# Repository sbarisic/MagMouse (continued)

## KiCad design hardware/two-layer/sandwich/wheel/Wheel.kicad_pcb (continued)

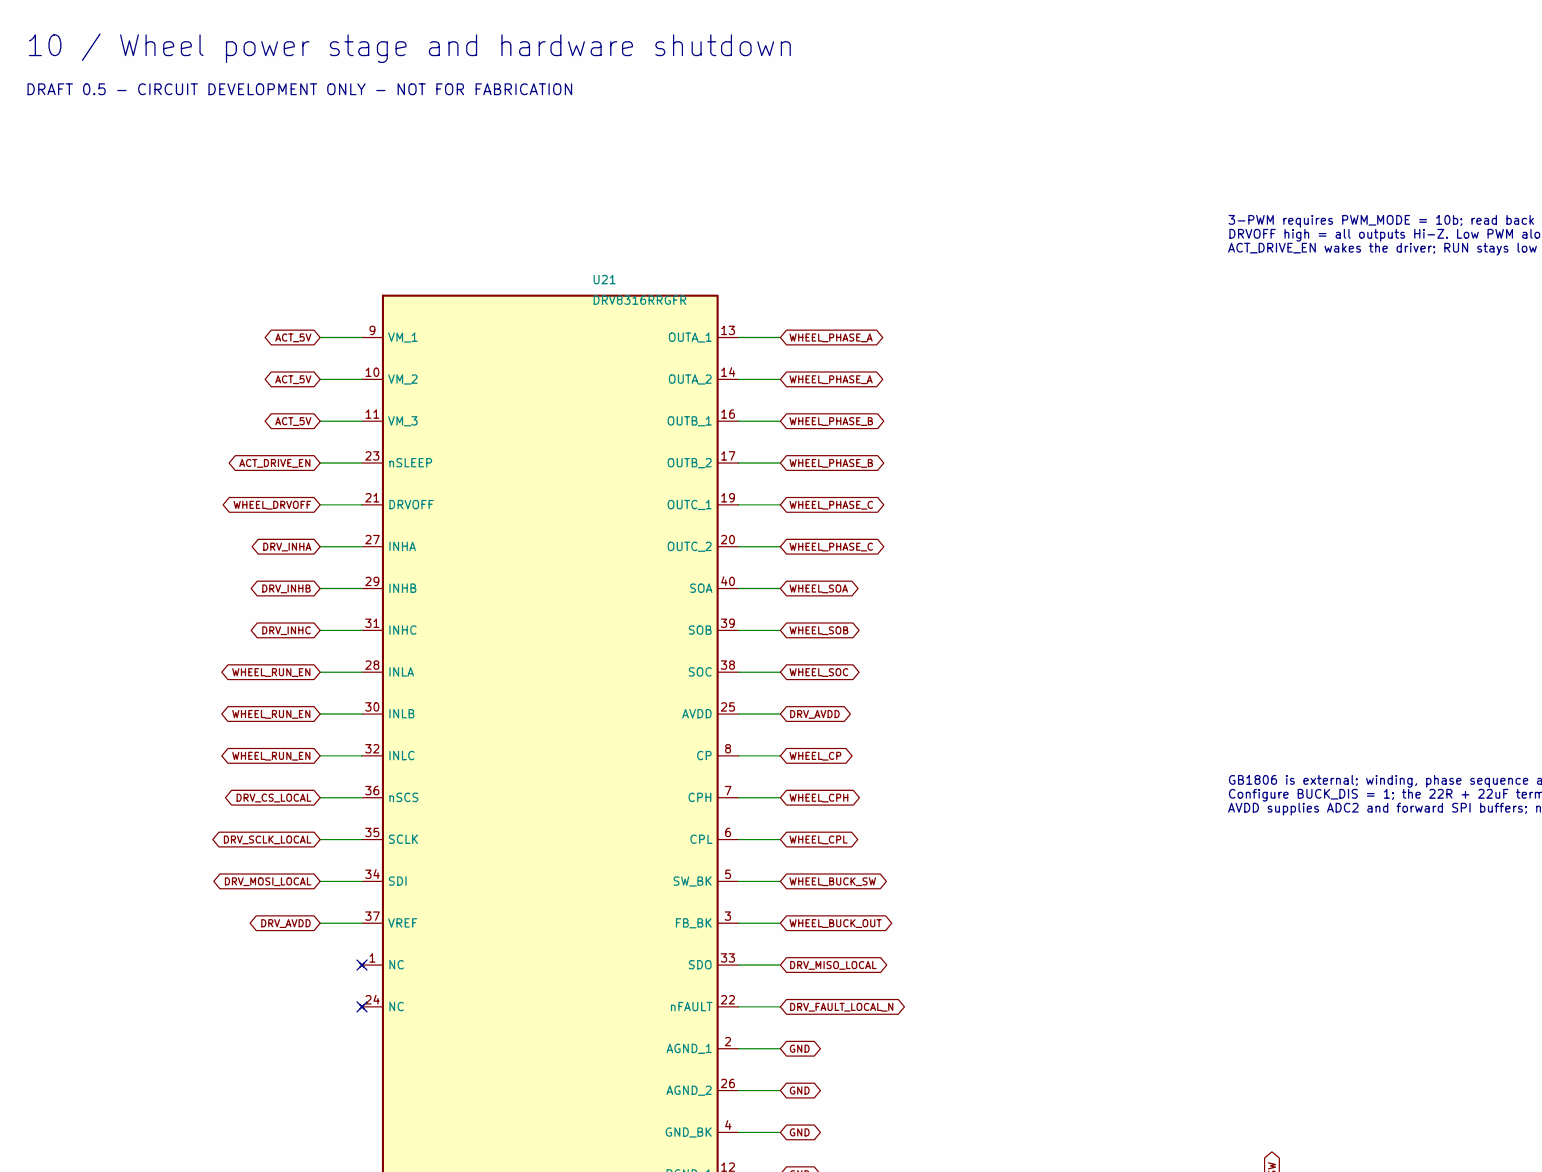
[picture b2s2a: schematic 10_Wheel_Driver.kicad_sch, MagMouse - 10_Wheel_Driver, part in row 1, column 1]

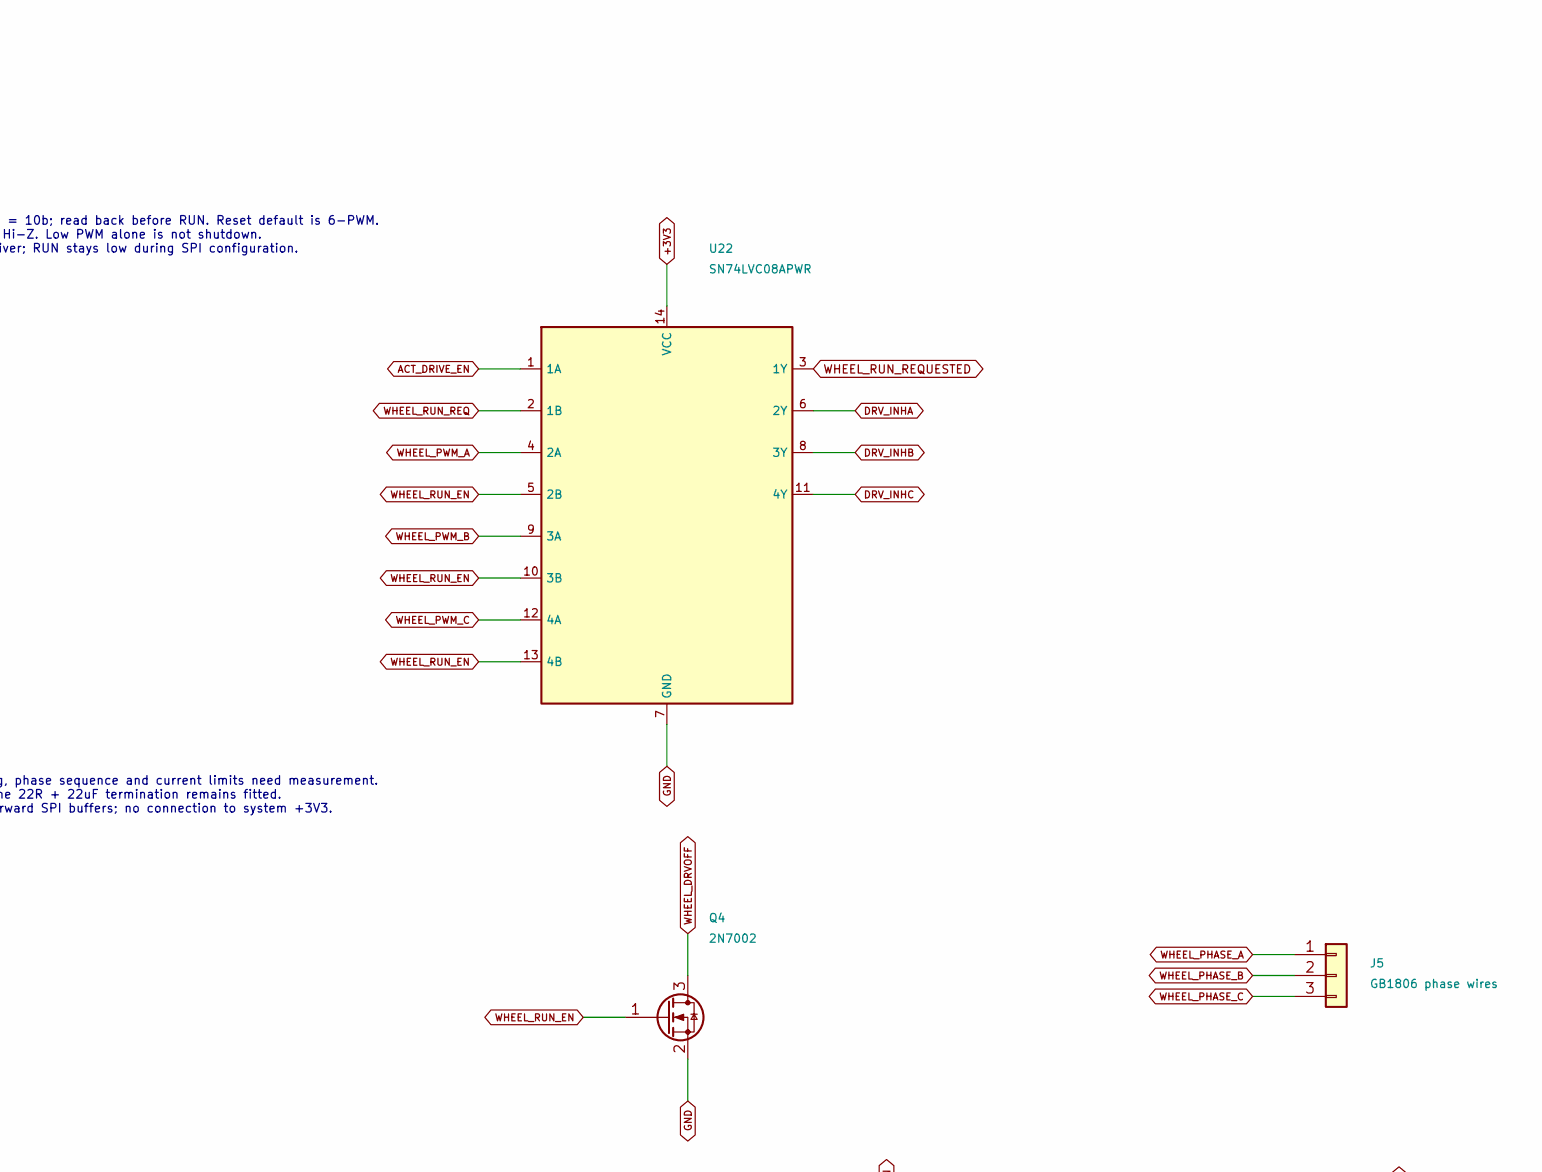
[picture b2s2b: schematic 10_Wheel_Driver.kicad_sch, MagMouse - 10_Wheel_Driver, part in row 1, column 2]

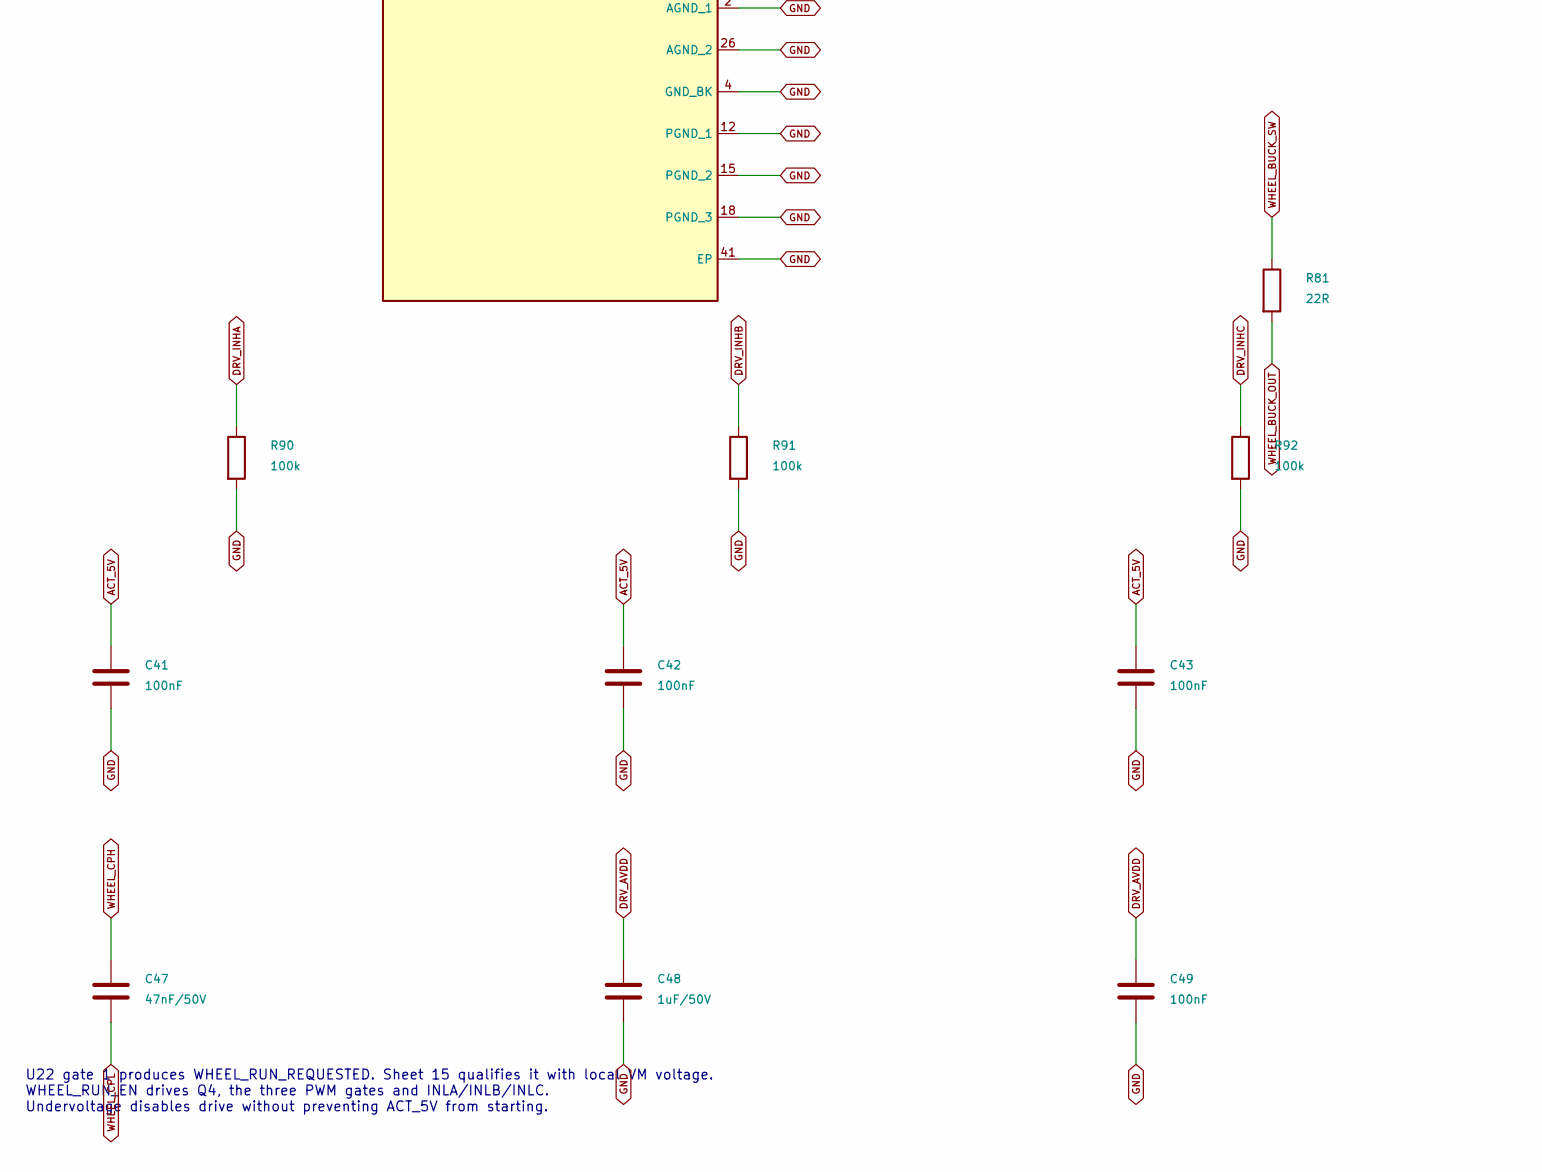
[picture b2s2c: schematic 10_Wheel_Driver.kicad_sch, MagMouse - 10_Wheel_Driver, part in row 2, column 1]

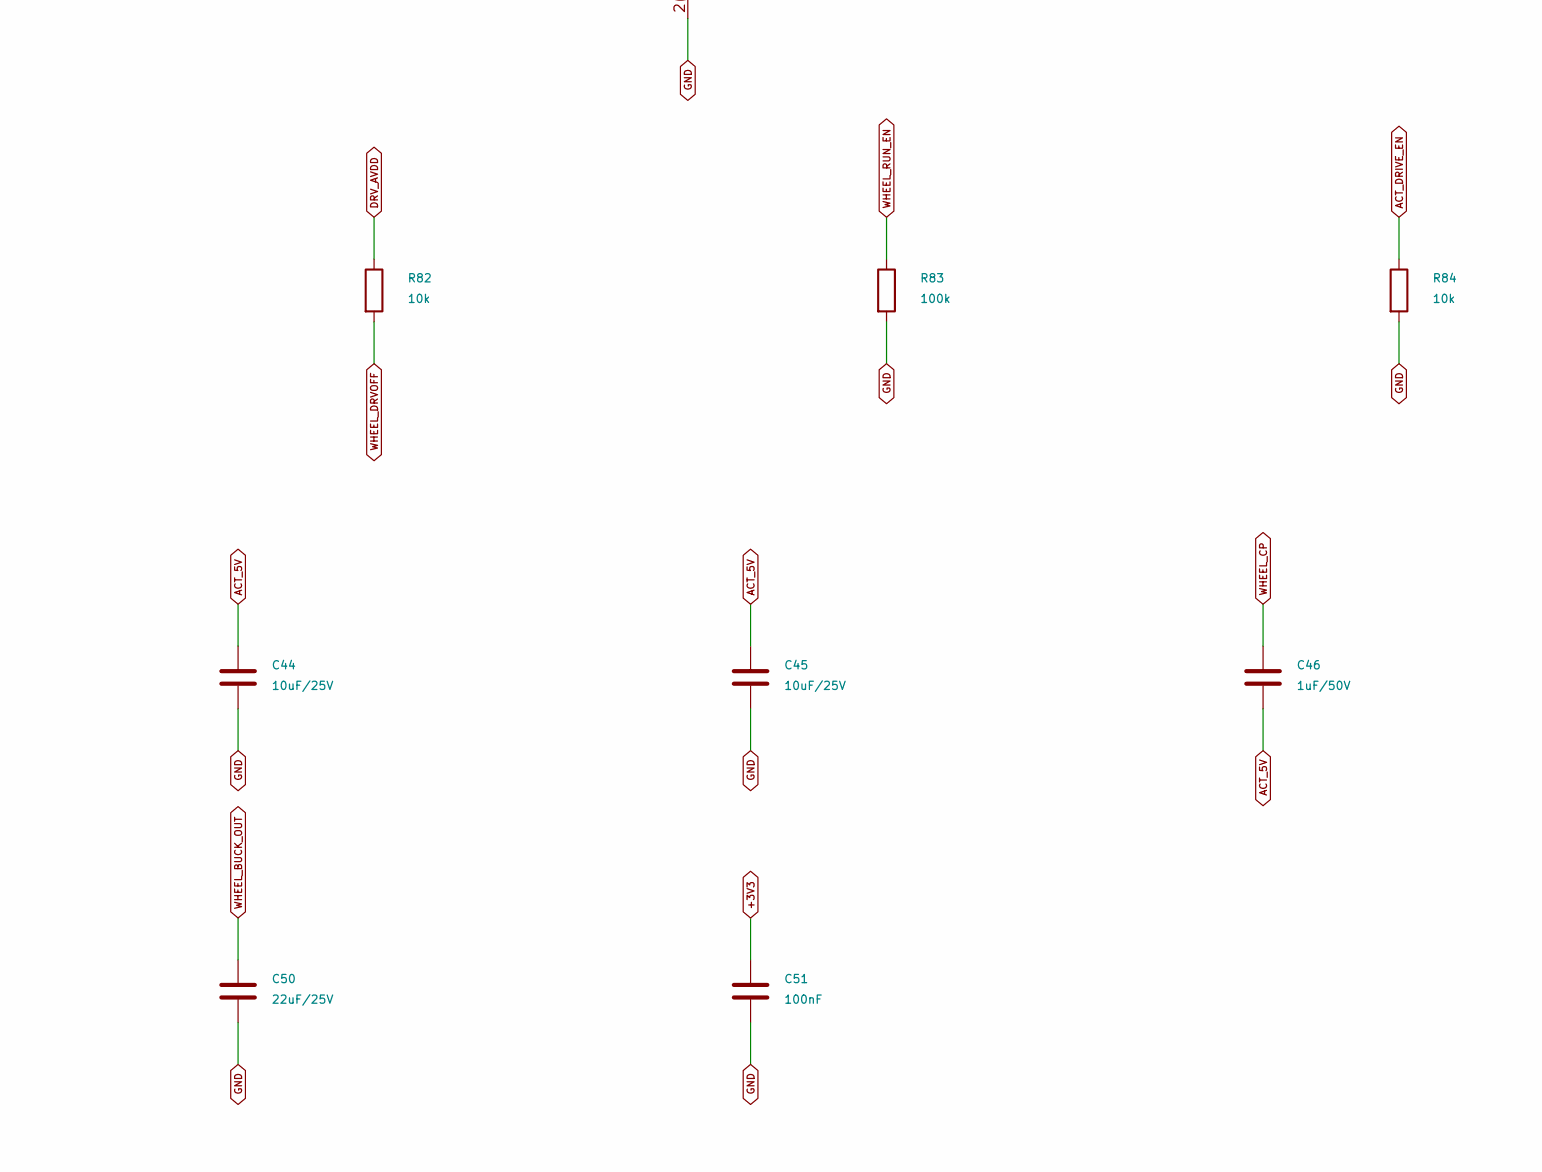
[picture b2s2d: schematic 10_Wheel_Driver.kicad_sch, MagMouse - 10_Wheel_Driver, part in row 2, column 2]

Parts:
C41, C42, C43, C49, C51: 100nF; C_1206_3216Metric; Rating 50 V, X7R, 10%; MPN CC1206KRX7R9BB104
C44, C45: 10uF/25V; C_1206_3216Metric; Rating 25 V, X5R, 10%; MPN CL31A106KAHNNNE
C46, C48: 1uF/50V; C_1206_3216Metric; Rating 50 V, X7R, 10%; MPN CL31B105KBHNNNE
C47: 47nF/50V; C_1206_3216Metric; Rating 50 V, X7R, 10%; MPN CC1206KRX7R9BB473
C50: 22uF/25V; C_1206_3216Metric; Rating 25 V, X5R, 10%; MPN CL31A226KAHNNNE
J5: GB1806 phase wires; MotorWire_3x1mm_P2.54mm
Q4: 2N7002; SOT-23; MPN 2N7002; LCSC C8545
R81: 22R; R_1206_3216Metric; Rating 0.25 W, 1%; MPN RC1206FR-0722RL
R82, R84: 10k; R_1206_3216Metric; Rating 0.25 W, 1%; MPN RC1206FR-0710KL
R83, R90, R91, R92: 100k; R_1206_3216Metric; Rating 0.25 W, 1%; MPN RC1206FR-07100KL
U21: DRV8316RRGFR; Texas_RGF0040E; MPN DRV8316RRGFR; LCSC C5218861
U22: SN74LVC08APWR; TSSOP-14_4.4x5mm_P0.65mm; MPN SN74LVC08APWR; LCSC C465737

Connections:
+3V3: C51.1, U22.14 (VCC); also elsewhere on the board
ACT_5V: C41.1, C42.1, C43.1, C44.1, C45.1, C46.2, U21.9 (VM_1), U21.10 (VM_2), U21.11 (VM_3); also elsewhere on the board
ACT_DRIVE_EN: R84.1, U21.23 (nSLEEP), U22.1 (1A); also elsewhere on the board
DRV_AVDD: C48.1, C49.1, R82.1, U21.25 (AVDD), U21.37 (VREF); also elsewhere on the board
DRV_CS_LOCAL: U21.36 (nSCS); also elsewhere on the board
DRV_FAULT_LOCAL_N: U21.22 (nFAULT); also elsewhere on the board
DRV_INHA: R90.1, U21.27 (INHA), U22.6 (2Y)
DRV_INHB: R91.1, U21.29 (INHB), U22.8 (3Y)
DRV_INHC: R92.1, U21.31 (INHC), U22.11 (4Y)
DRV_MISO_LOCAL: U21.33 (SDO); also elsewhere on the board
DRV_MOSI_LOCAL: U21.34 (SDI); also elsewhere on the board
DRV_SCLK_LOCAL: U21.35 (SCLK); also elsewhere on the board
GND: C41.2, C42.2, C43.2, C44.2, C45.2, C48.2, C49.2, C50.2, C51.2, Q4.2 (S), R83.2, R84.2, R90.2, R91.2, R92.2, U21.2 (AGND_1), U21.4 (GND_BK), U21.12 (PGND_1), U21.15 (PGND_2), U21.18 (PGND_3), U21.26 (AGND_2), U21.41 (EP), U22.7 (GND); also elsewhere on the board
WHEEL_BUCK_OUT: C50.1, R81.2, U21.3 (FB_BK)
WHEEL_BUCK_SW: R81.1, U21.5 (SW_BK)
WHEEL_CP: C46.1, U21.8 (CP)
WHEEL_CPH: C47.1, U21.7 (CPH)
WHEEL_CPL: C47.2, U21.6 (CPL)
WHEEL_DRVOFF: Q4.3 (D), R82.2, U21.21 (DRVOFF)
WHEEL_PHASE_A: J5.1, U21.13 (OUTA_1), U21.14 (OUTA_2)
WHEEL_PHASE_B: J5.2, U21.16 (OUTB_1), U21.17 (OUTB_2)
WHEEL_PHASE_C: J5.3, U21.19 (OUTC_1), U21.20 (OUTC_2)
WHEEL_PWM_A: U22.4 (2A); also elsewhere on the board
WHEEL_PWM_B: U22.9 (3A); also elsewhere on the board
WHEEL_PWM_C: U22.12 (4A); also elsewhere on the board
WHEEL_RUN_EN: Q4.1 (G), R83.1, U21.28 (INLA), U21.30 (INLB), U21.32 (INLC), U22.5 (2B), U22.10 (3B), U22.13 (4B); also elsewhere on the board
WHEEL_RUN_REQ: U22.2 (1B); also elsewhere on the board
WHEEL_RUN_REQUESTED: U22.3 (1Y); also elsewhere on the board
WHEEL_SOA: U21.40 (SOA); also elsewhere on the board
WHEEL_SOB: U21.39 (SOB); also elsewhere on the board
WHEEL_SOC: U21.38 (SOC); also elsewhere on the board

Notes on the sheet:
10 / Wheel power stage and hardware shutdown
DRAFT 0.5 - CIRCUIT DEVELOPMENT ONLY - NOT FOR FABRICATION
3-PWM requires PWM_MODE = 10b; read back before RUN. Reset default is 6-PWM. DRVOFF high = all outputs Hi-Z. Low PWM alone is not shutdown. ACT_DRIVE_EN wakes the driver; RUN stays low during SPI configuration.
GB1806 is external; winding, phase sequence and current limits need measurement. Configure BUCK_DIS = 1; the 22R + 22uF termination remains fitted. AVDD supplies ADC2 and forward SPI buffers; no connection to system +3V3.
U22 gate 1 produces WHEEL_RUN_REQUESTED. Sheet 15 qualifies it with local VM voltage. WHEEL_RUN_EN drives Q4, the three PWM gates and INLA/INLB/INLC. Undervoltage disables drive without preventing ACT_5V from starting.

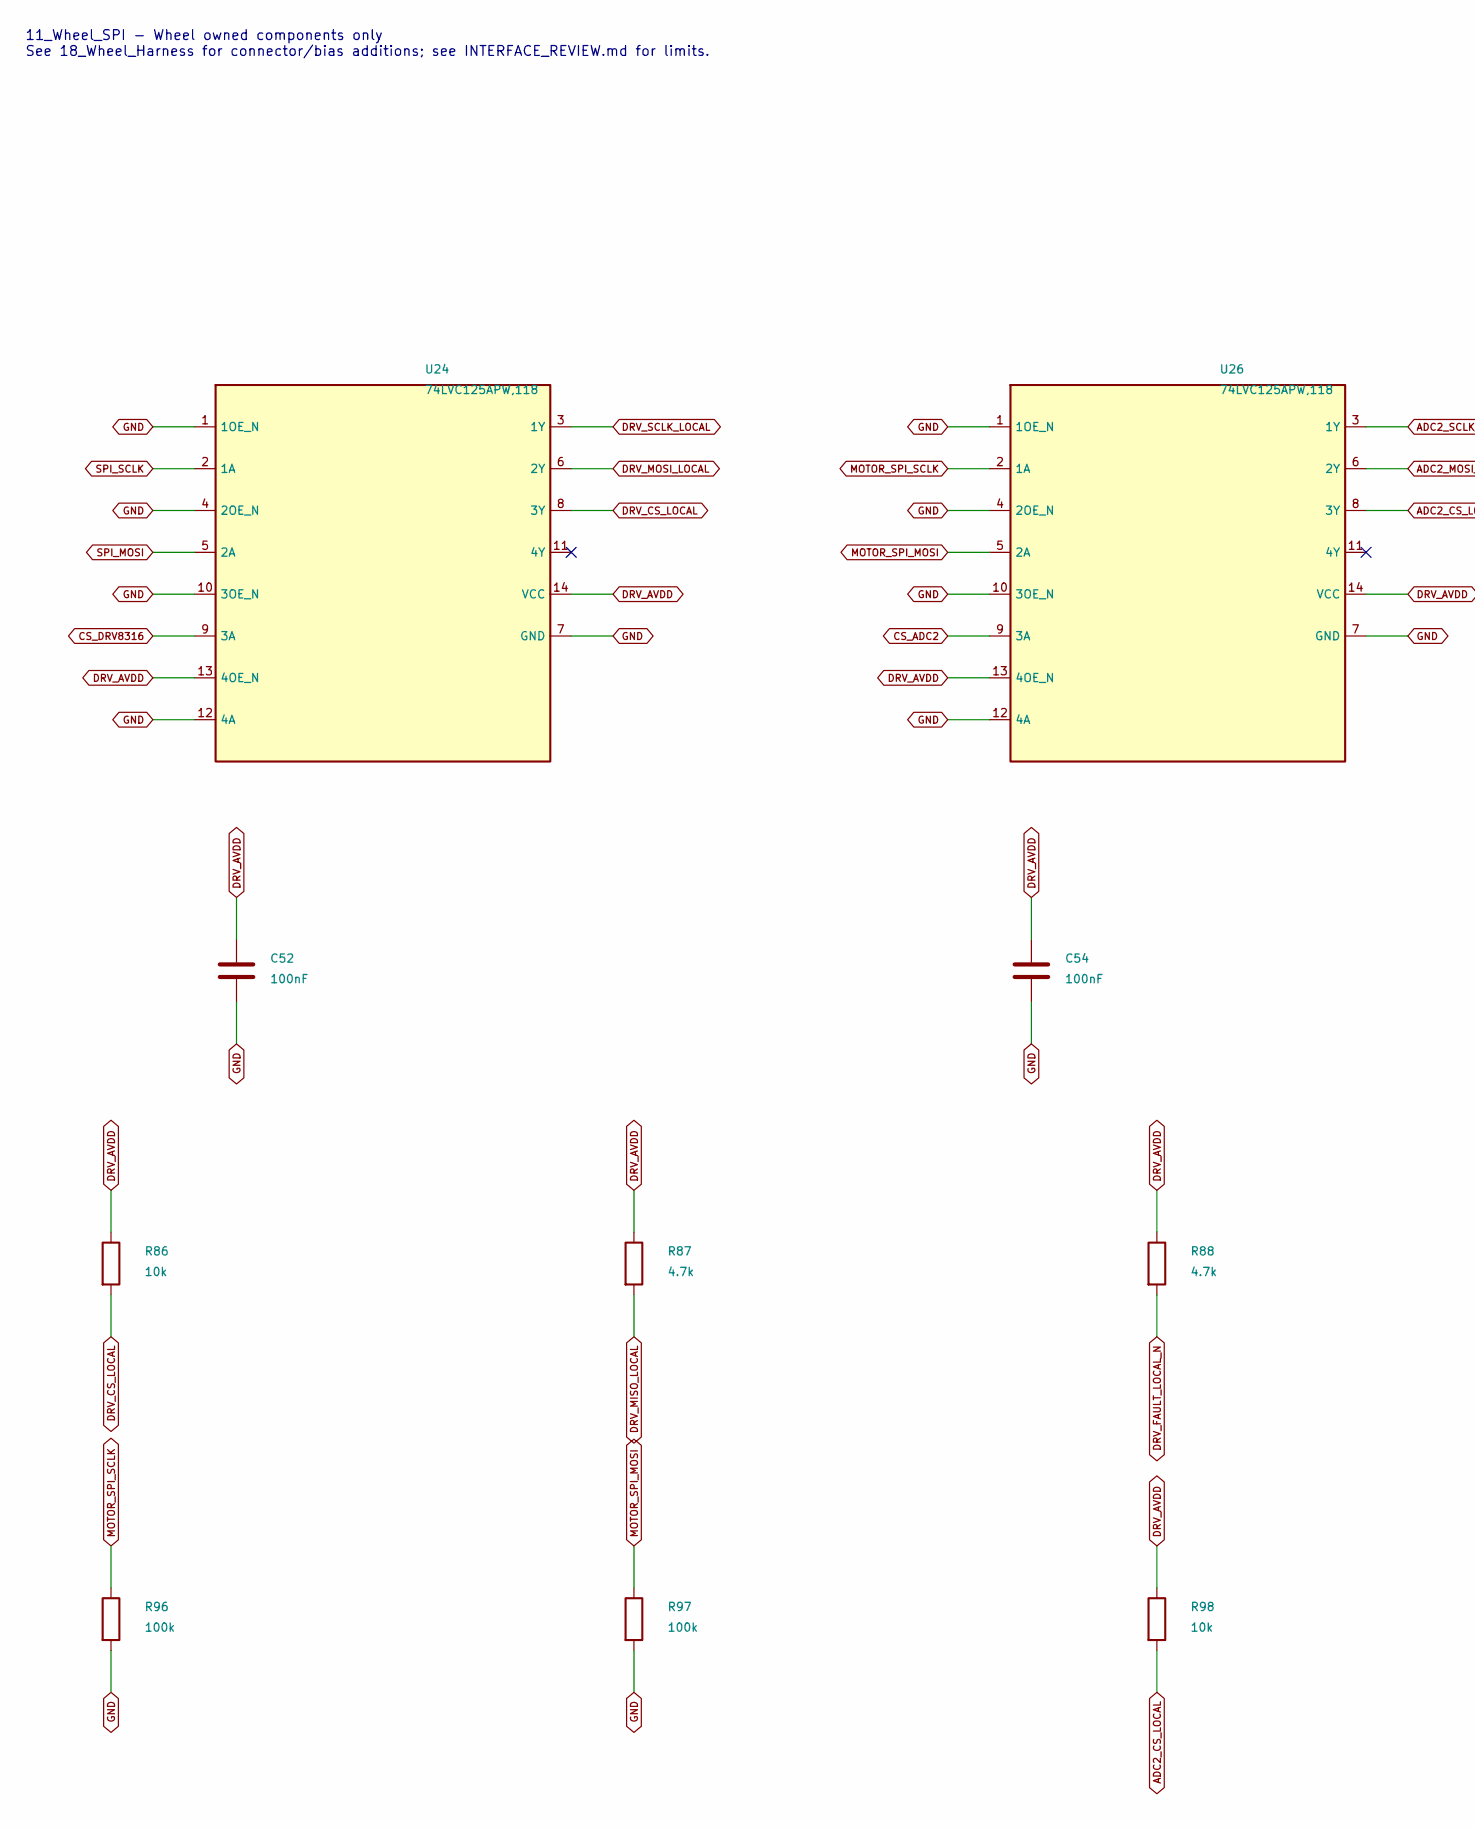
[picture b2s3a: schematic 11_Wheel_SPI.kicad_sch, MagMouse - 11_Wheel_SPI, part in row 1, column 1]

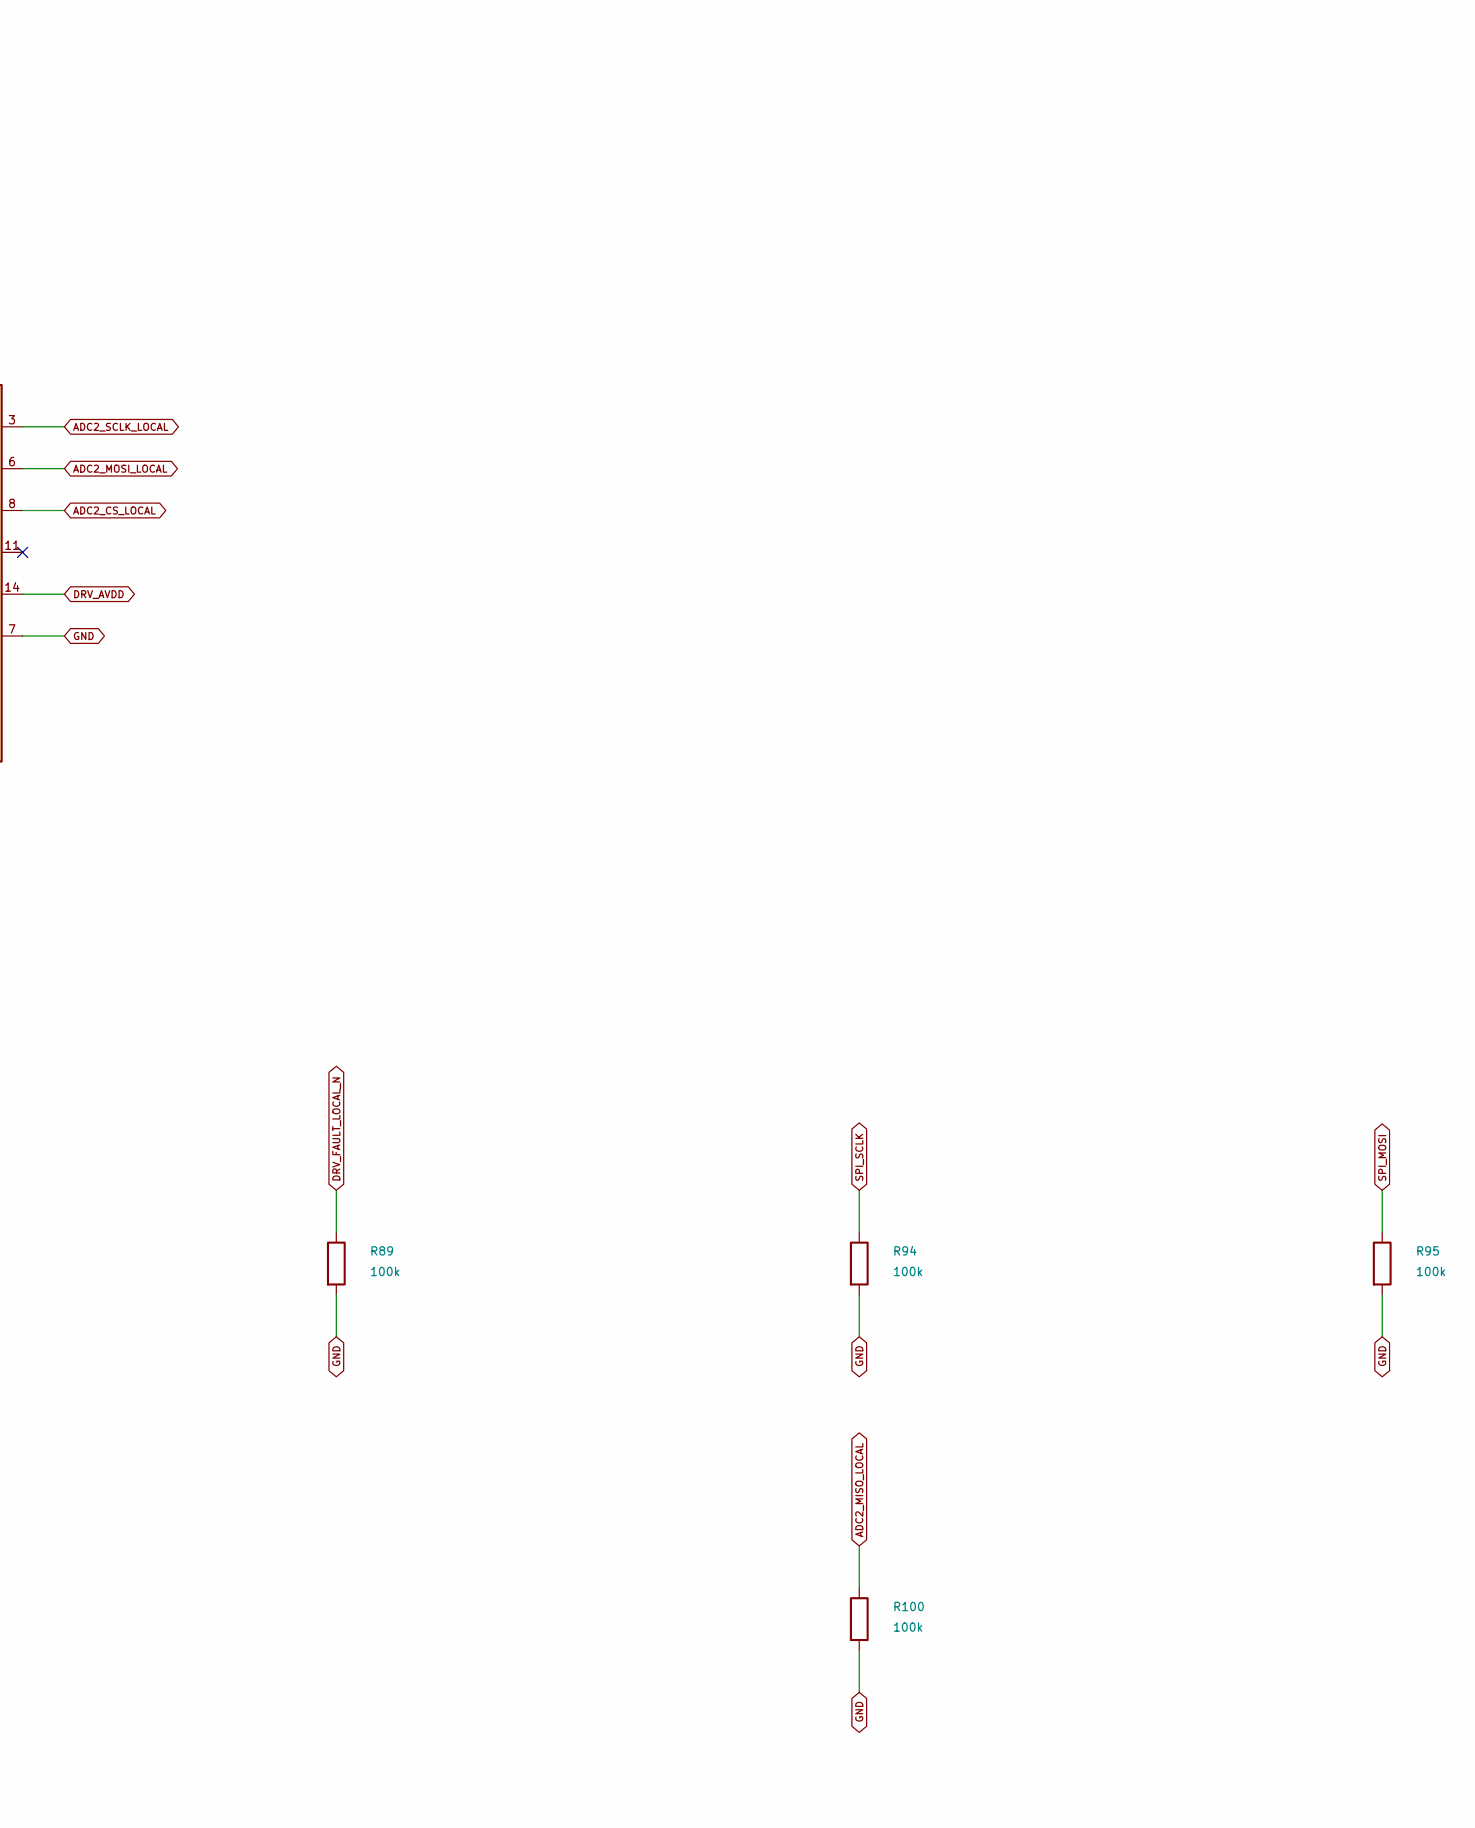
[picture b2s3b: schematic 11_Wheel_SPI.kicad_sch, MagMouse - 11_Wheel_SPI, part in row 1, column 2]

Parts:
C52, C54: 100nF; C_1206_3216Metric; Rating 50 V, X7R, 10%; MPN CC1206KRX7R9BB104
R86, R98: 10k; R_1206_3216Metric; Rating 0.25 W, 1%; MPN RC1206FR-0710KL
R87, R88: 4.7k; R_1206_3216Metric; Rating 0.25 W, 1%; MPN RC1206FR-074K7L
R89, R94, R95, R96, R97, R100: 100k; R_1206_3216Metric; Rating 0.25 W, 1%; MPN RC1206FR-07100KL
U24: 74LVC125APW,118; TSSOP-14_4.4x5mm_P0.65mm_InsetPin1; MPN 74LVC125APW,118; LCSC C6059
U26: 74LVC125APW,118; TSSOP-14_4.4x5mm_P0.65mm; MPN 74LVC125APW,118; LCSC C6059

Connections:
ADC2_CS_LOCAL: R98.2, U26.8 (3Y); also elsewhere on the board
ADC2_MISO_LOCAL: R100.1; also elsewhere on the board
ADC2_MOSI_LOCAL: U26.6 (2Y); also elsewhere on the board
ADC2_SCLK_LOCAL: U26.3 (1Y); also elsewhere on the board
CS_ADC2: U26.9 (3A); also elsewhere on the board
CS_DRV8316: U24.9 (3A); also elsewhere on the board
DRV_AVDD: C52.1, C54.1, R86.1, R87.1, R88.1, R98.1, U24.13 (4OE_N), U24.14 (VCC), U26.13 (4OE_N), U26.14 (VCC); also elsewhere on the board
DRV_CS_LOCAL: R86.2, U24.8 (3Y); also elsewhere on the board
DRV_FAULT_LOCAL_N: R88.2, R89.1; also elsewhere on the board
DRV_MISO_LOCAL: R87.2; also elsewhere on the board
DRV_MOSI_LOCAL: U24.6 (2Y); also elsewhere on the board
DRV_SCLK_LOCAL: U24.3 (1Y); also elsewhere on the board
GND: C52.2, C54.2, R89.2, R94.2, R95.2, R96.2, R97.2, R100.2, U24.1 (1OE_N), U24.4 (2OE_N), U24.7 (GND), U24.10 (3OE_N), U24.12 (4A), U26.1 (1OE_N), U26.4 (2OE_N), U26.7 (GND), U26.10 (3OE_N), U26.12 (4A); also elsewhere on the board
MOTOR_SPI_MOSI: R97.1, U26.5 (2A); also elsewhere on the board
MOTOR_SPI_SCLK: R96.1, U26.2 (1A); also elsewhere on the board
SPI_MOSI: R95.1, U24.5 (2A); also elsewhere on the board
SPI_SCLK: R94.1, U24.2 (1A); also elsewhere on the board

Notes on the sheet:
11_Wheel_SPI - Wheel owned components only See 18_Wheel_Harness for connector/bias additions; see INTERFACE_REVIEW.md for limits.

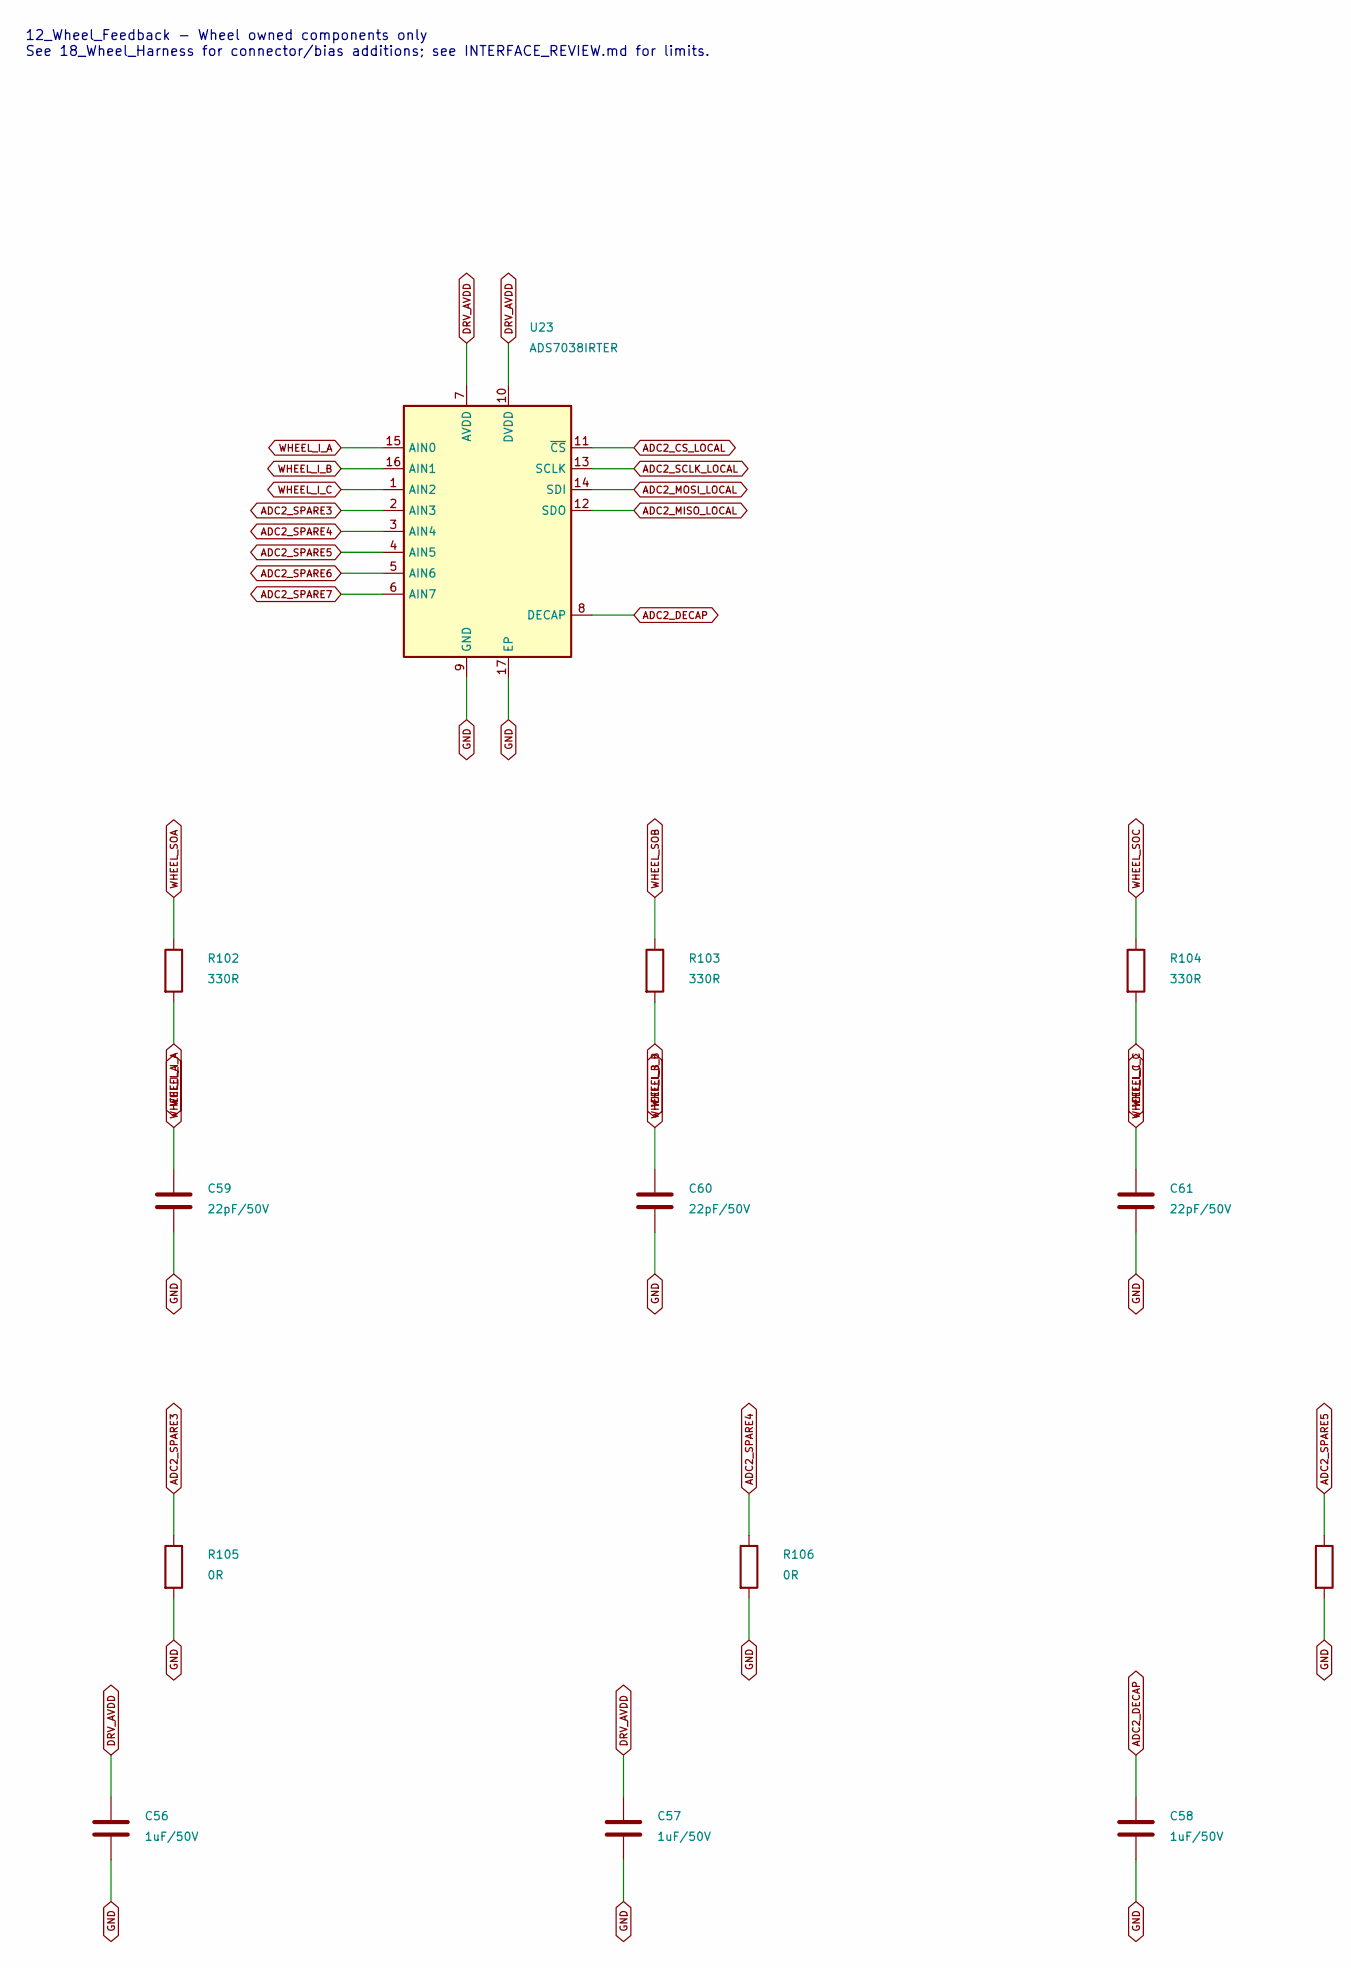
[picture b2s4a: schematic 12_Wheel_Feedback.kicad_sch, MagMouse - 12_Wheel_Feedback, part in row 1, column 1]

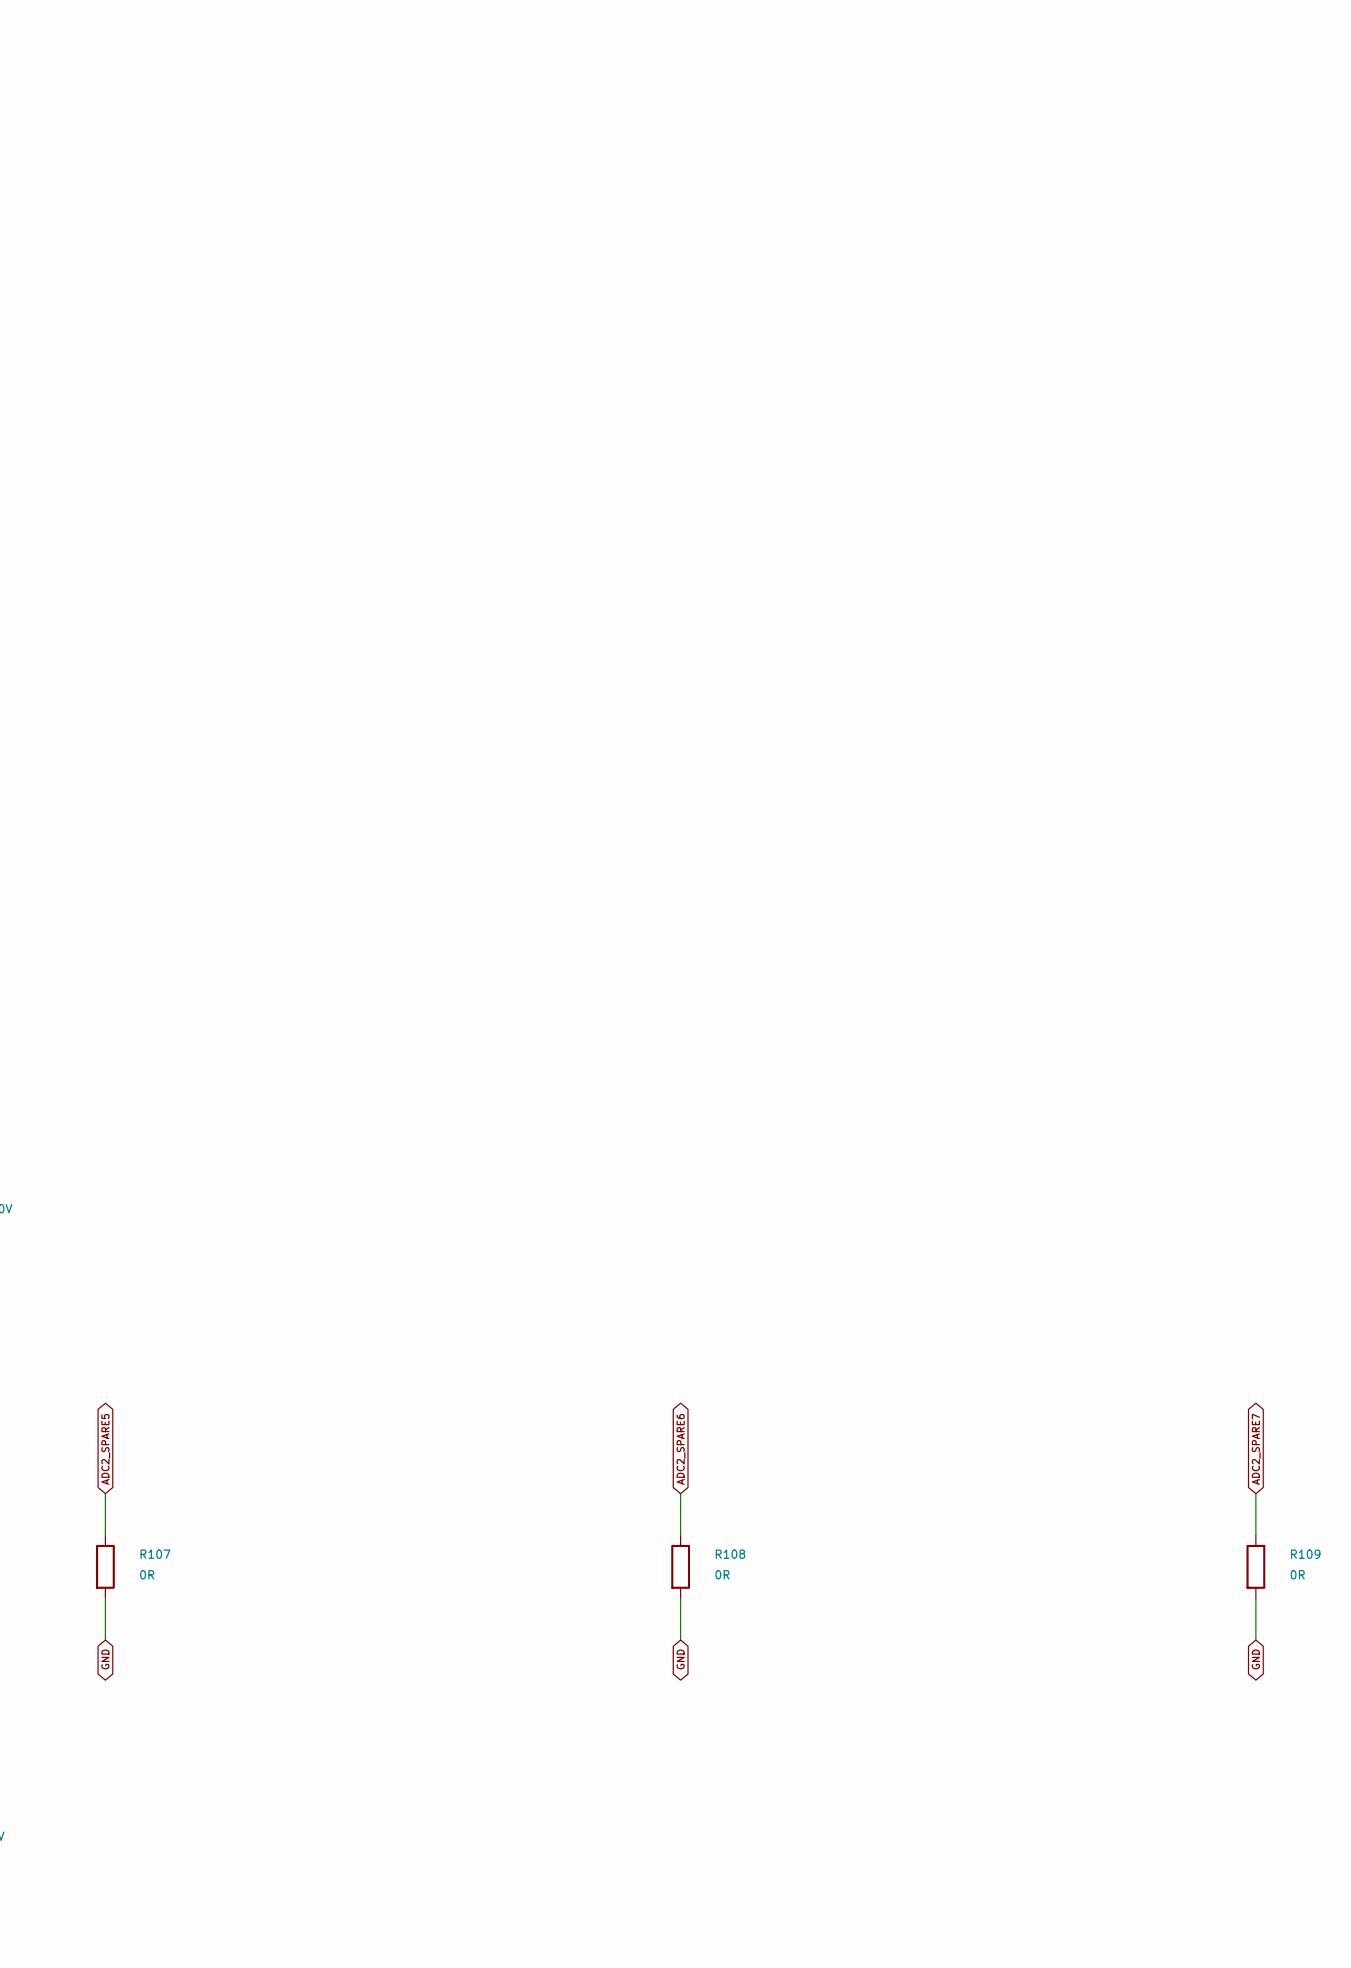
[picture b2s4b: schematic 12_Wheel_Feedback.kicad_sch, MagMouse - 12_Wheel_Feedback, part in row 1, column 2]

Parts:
C56, C57, C58: 1uF/50V; C_1206_3216Metric; Rating 50 V, X7R, 10%; MPN CL31B105KBHNNNE
C59, C60, C61: 22pF/50V; C_1206_3216Metric; Rating 50 V, C0G/NP0, 5%; MPN CC1206JRNPO9BN220
R102, R103, R104: 330R; R_1206_3216Metric; Rating 0.25 W, 1%; MPN RC1206FR-07330RL
R105, R106, R107, R108, R109: 0R; R_1206_3216Metric; Rating Jumper, 2 A; MPN RC1206JR-070RL
U23: ADS7038IRTER; WQFN-16-1EP_3x3mm_P0.5mm_EP1.68x1.68mm; MPN ADS7038IRTER; LCSC C2871580

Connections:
ADC2_CS_LOCAL: U23.11 (~CS); also elsewhere on the board
ADC2_DECAP: C58.1, U23.8 (DECAP)
ADC2_MISO_LOCAL: U23.12 (SDO); also elsewhere on the board
ADC2_MOSI_LOCAL: U23.14 (SDI); also elsewhere on the board
ADC2_SCLK_LOCAL: U23.13 (SCLK); also elsewhere on the board
ADC2_SPARE3: R105.1, U23.2 (AIN3)
ADC2_SPARE4: R106.1, U23.3 (AIN4)
ADC2_SPARE5: R107.1, U23.4 (AIN5)
ADC2_SPARE6: R108.1, U23.5 (AIN6)
ADC2_SPARE7: R109.1, U23.6 (AIN7)
DRV_AVDD: C56.1, C57.1, U23.7 (AVDD), U23.10 (DVDD); also elsewhere on the board
GND: C56.2, C57.2, C58.2, C59.2, C60.2, C61.2, R105.2, R106.2, R107.2, R108.2, R109.2, U23.9 (GND), U23.17 (EP); also elsewhere on the board
WHEEL_I_A: C59.1, R102.2, U23.15 (AIN0)
WHEEL_I_B: C60.1, R103.2, U23.16 (AIN1)
WHEEL_I_C: C61.1, R104.2, U23.1 (AIN2)
WHEEL_SOA: R102.1; also elsewhere on the board
WHEEL_SOB: R103.1; also elsewhere on the board
WHEEL_SOC: R104.1; also elsewhere on the board

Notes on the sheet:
12_Wheel_Feedback - Wheel owned components only See 18_Wheel_Harness for connector/bias additions; see INTERFACE_REVIEW.md for limits.
